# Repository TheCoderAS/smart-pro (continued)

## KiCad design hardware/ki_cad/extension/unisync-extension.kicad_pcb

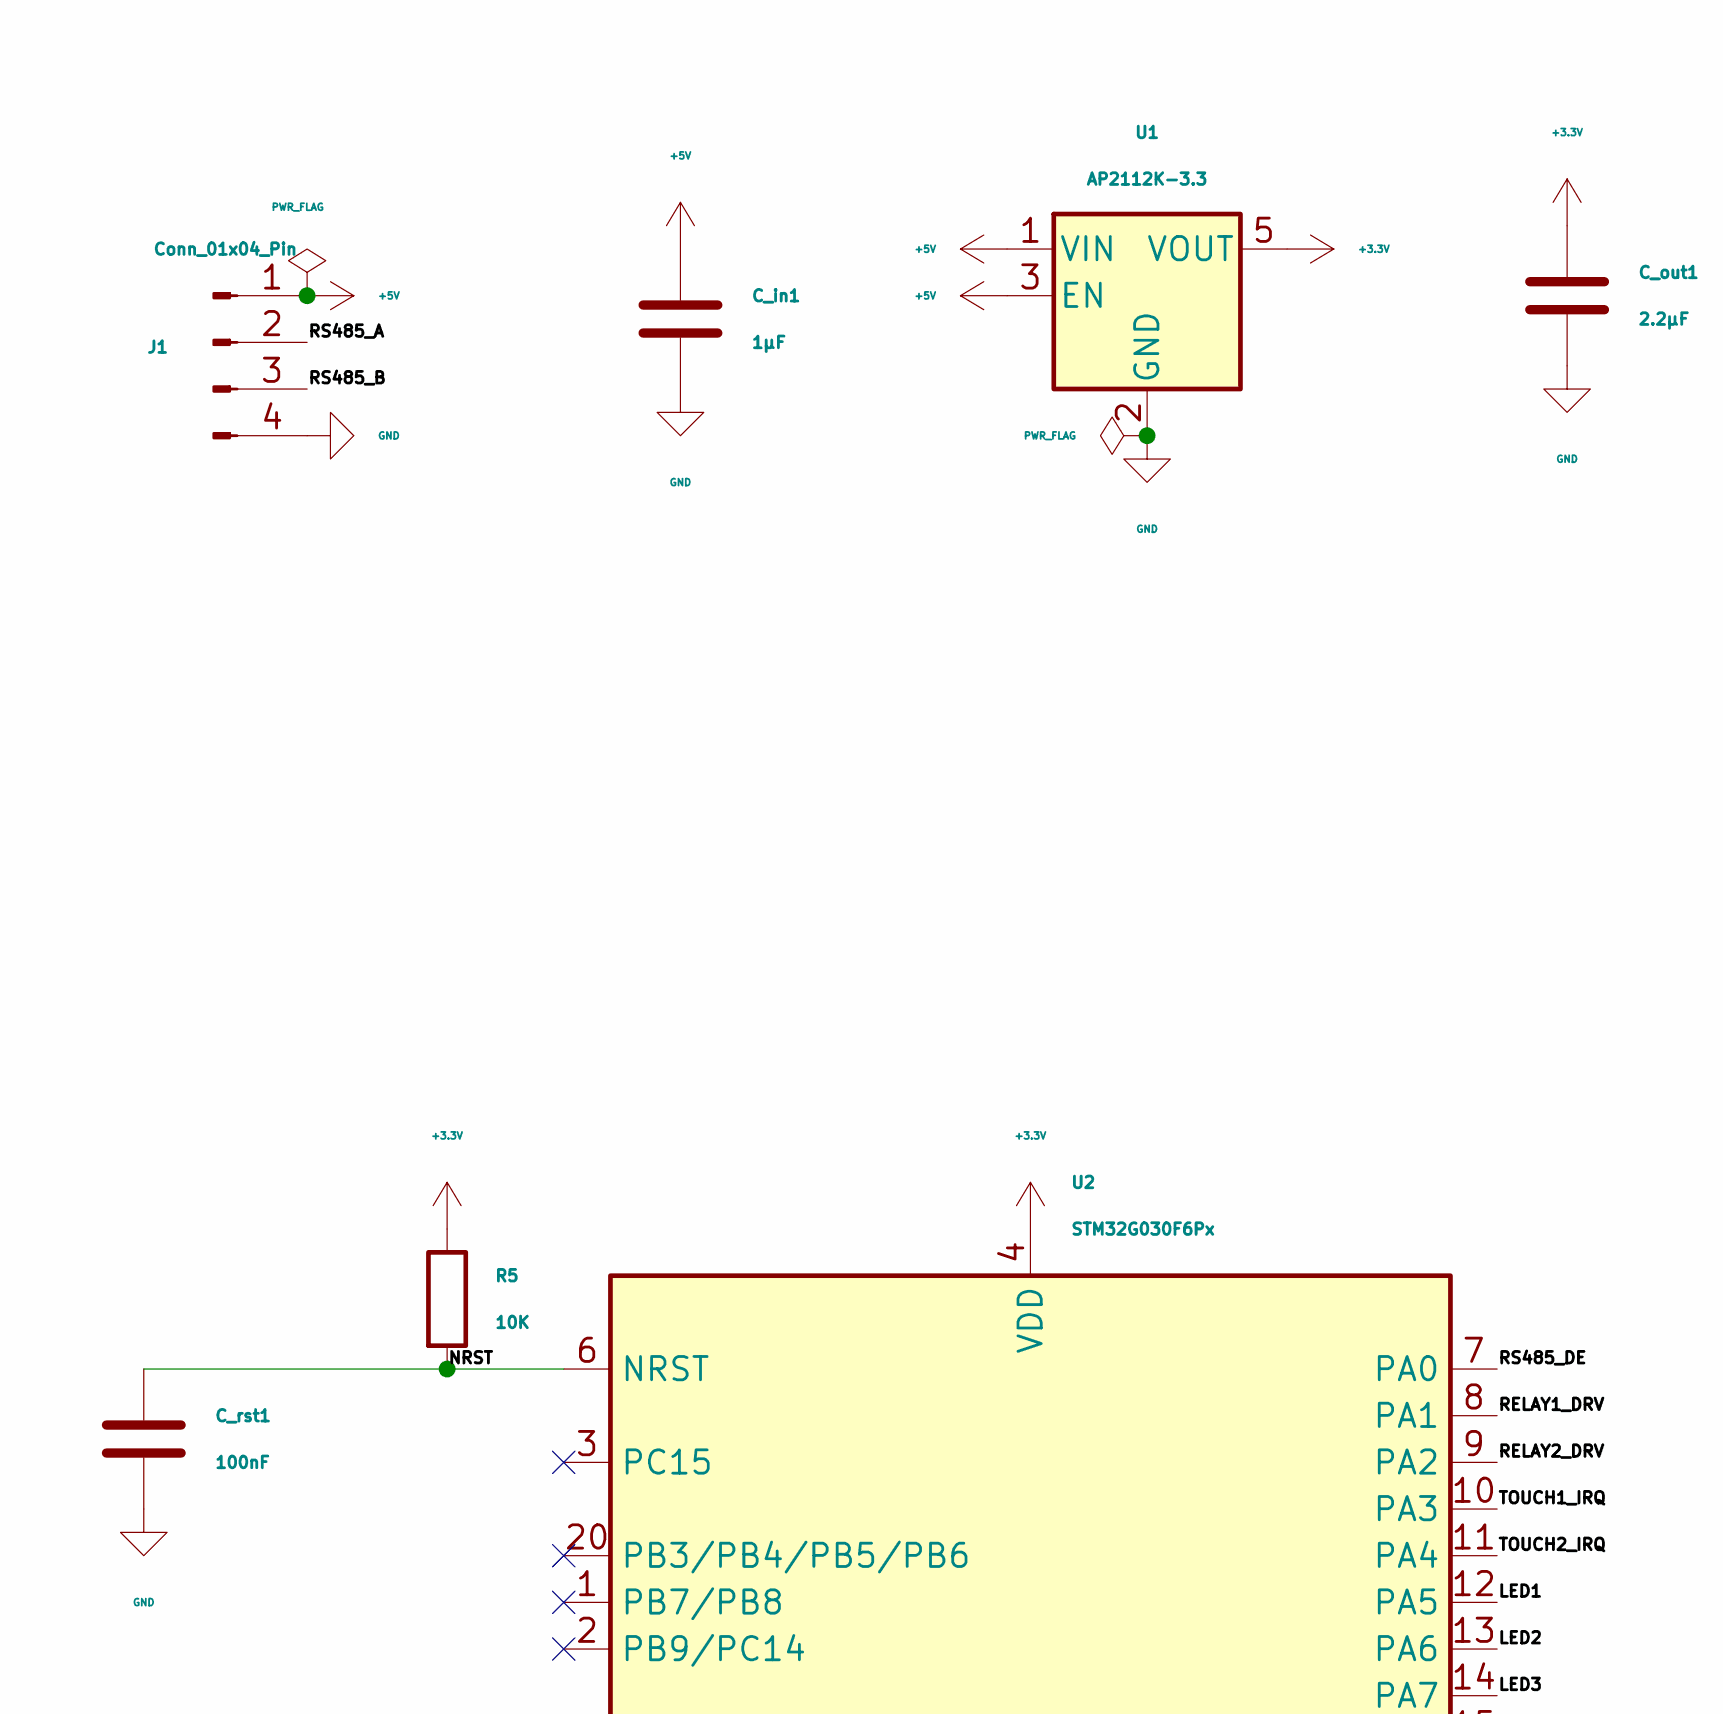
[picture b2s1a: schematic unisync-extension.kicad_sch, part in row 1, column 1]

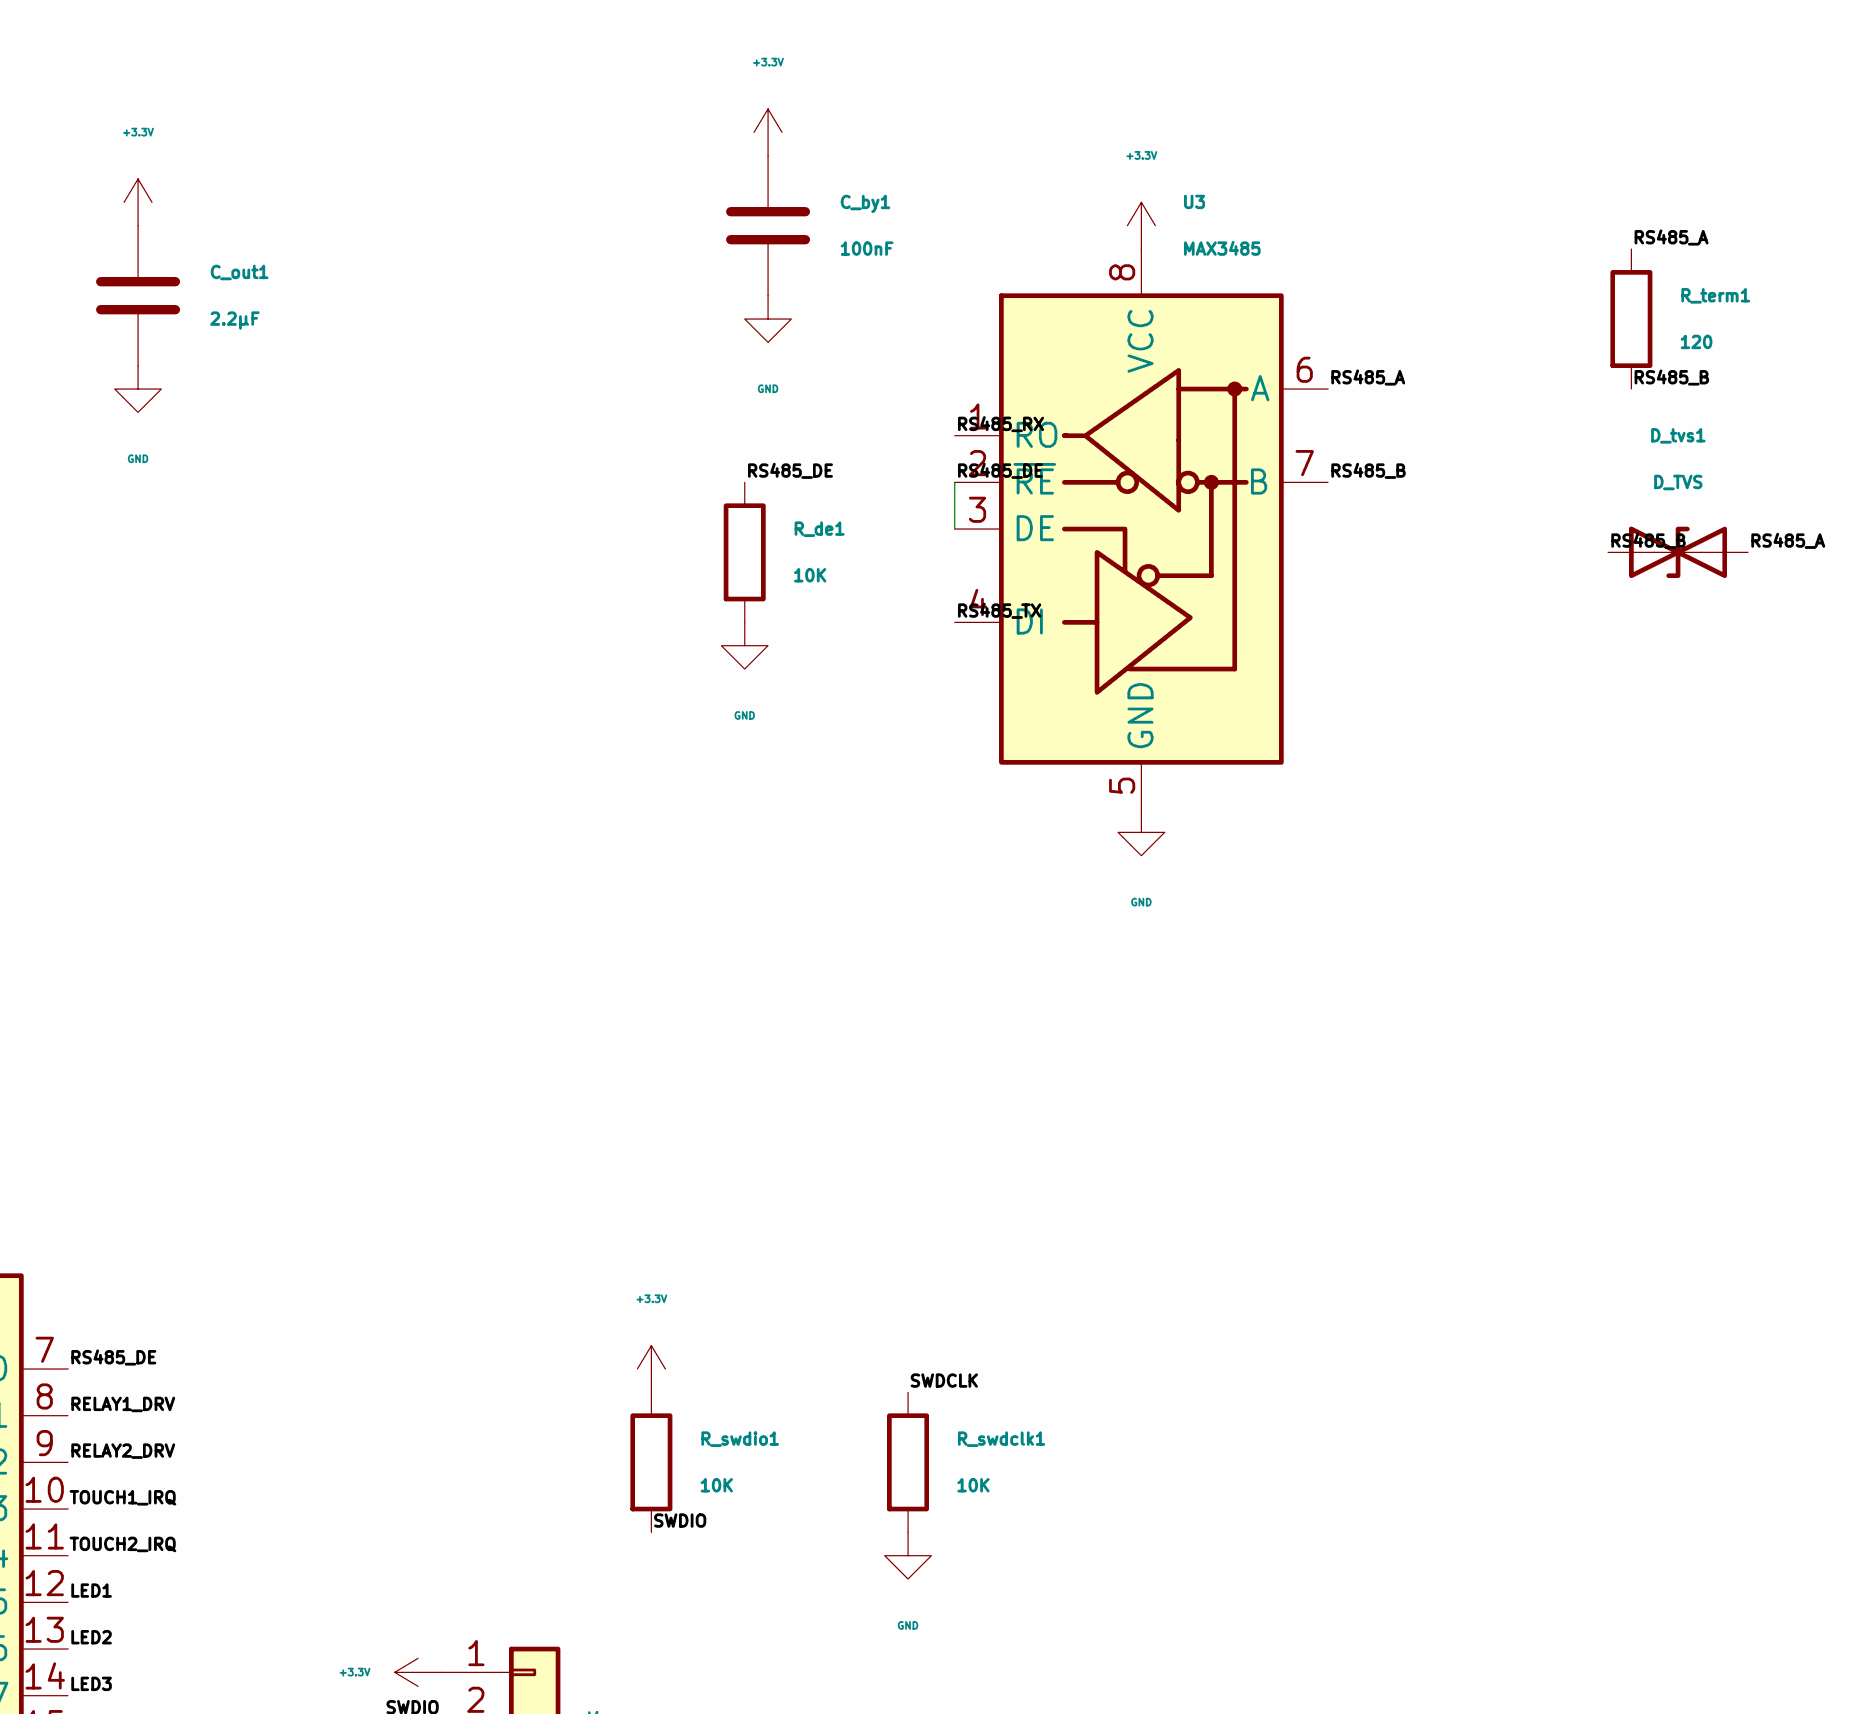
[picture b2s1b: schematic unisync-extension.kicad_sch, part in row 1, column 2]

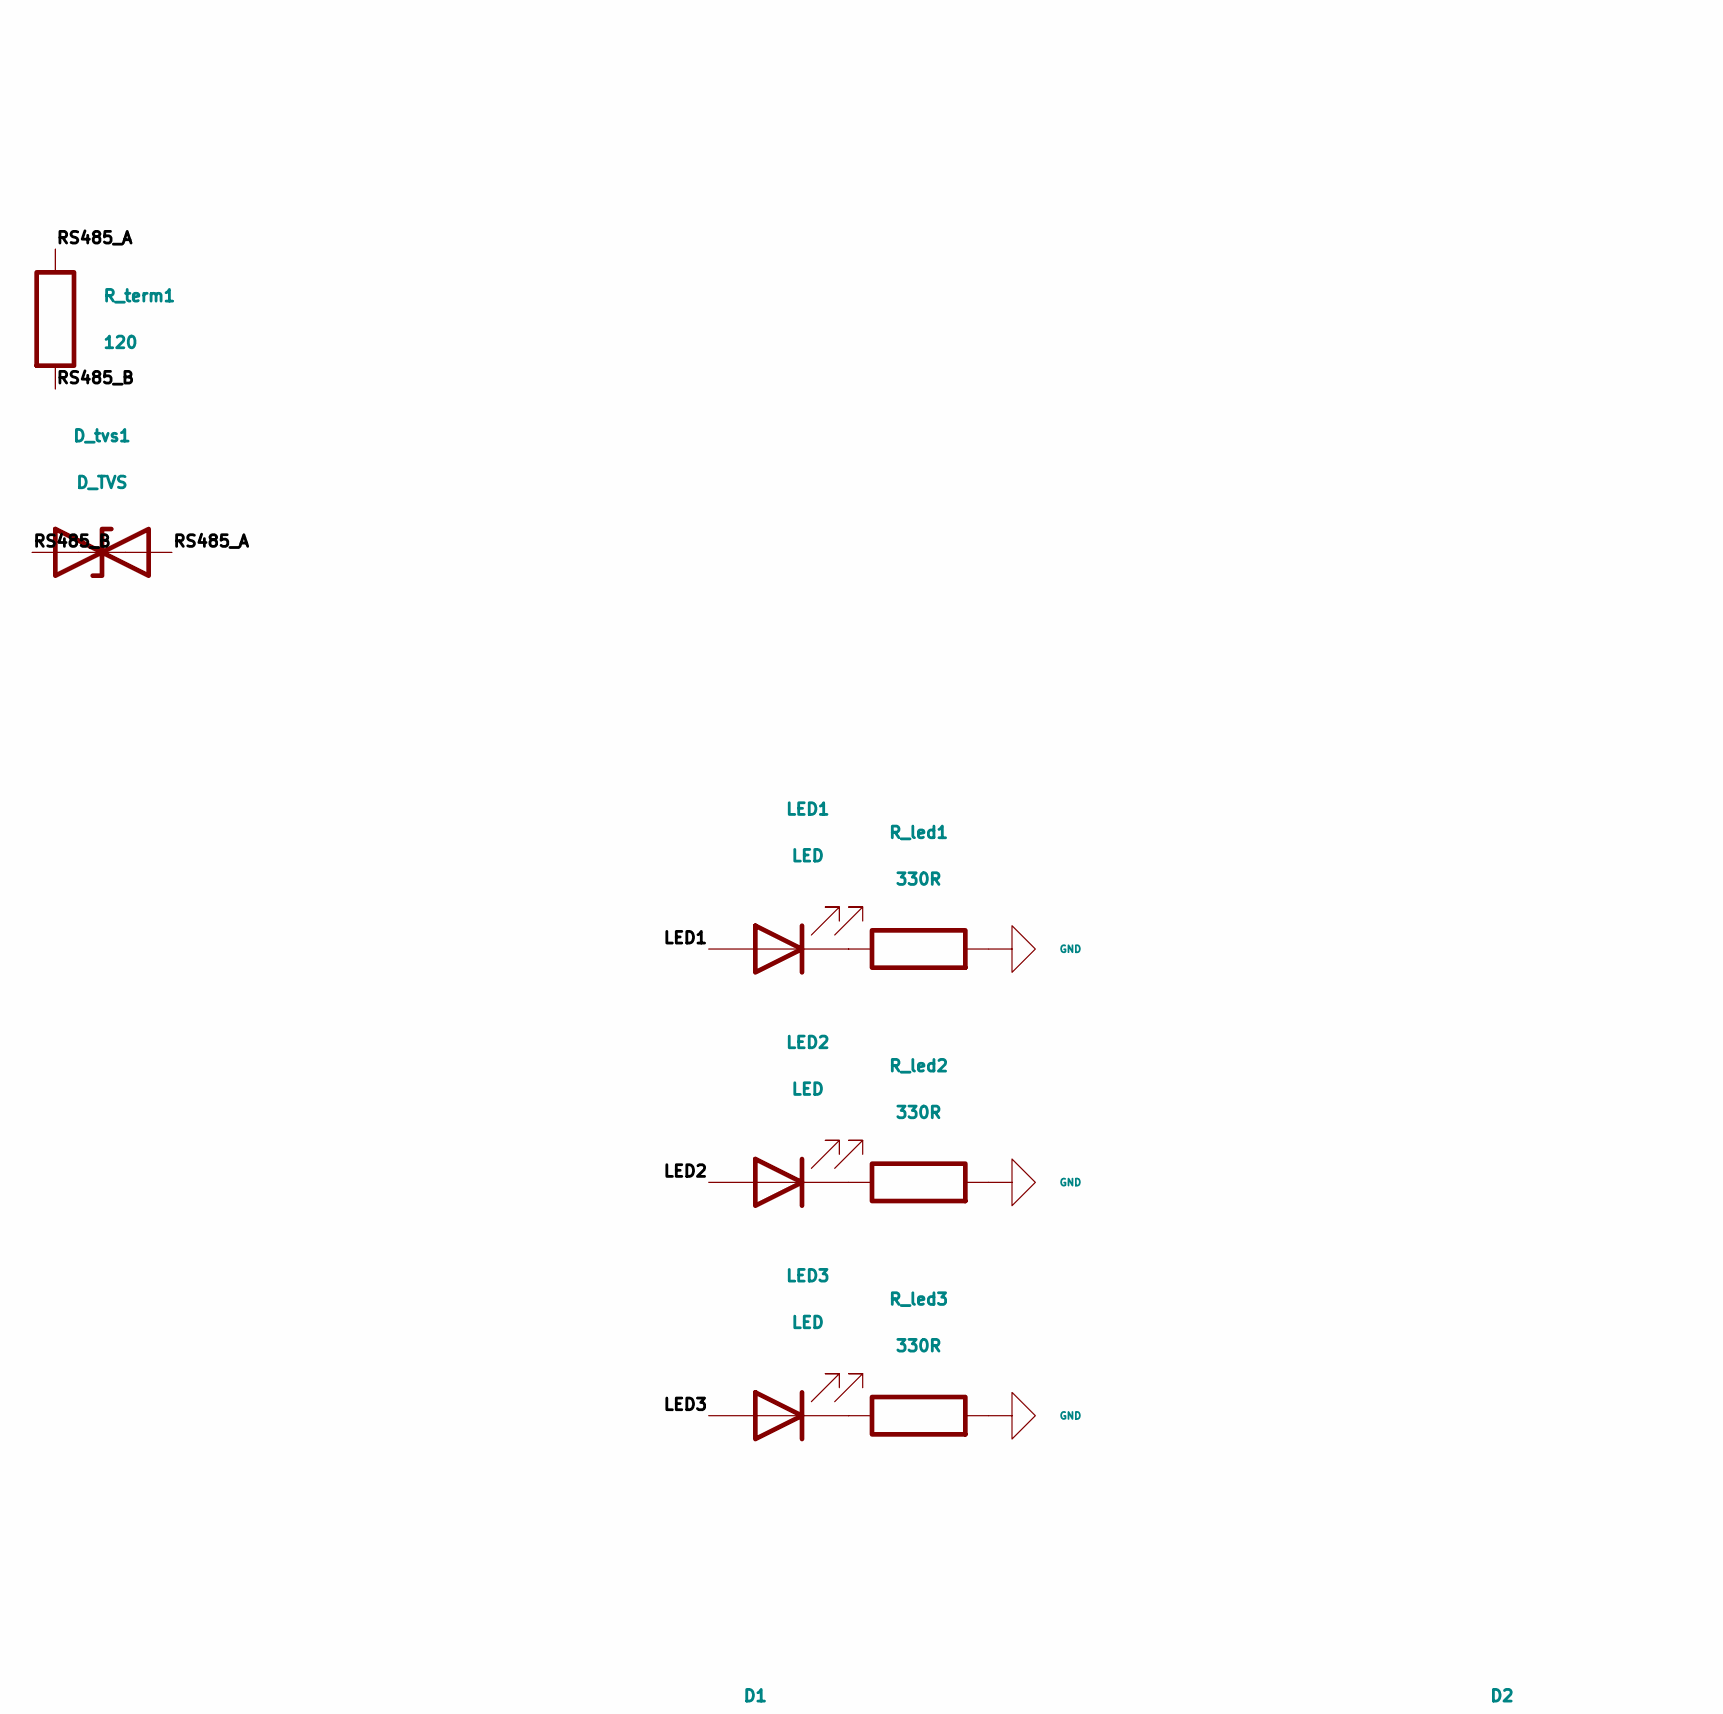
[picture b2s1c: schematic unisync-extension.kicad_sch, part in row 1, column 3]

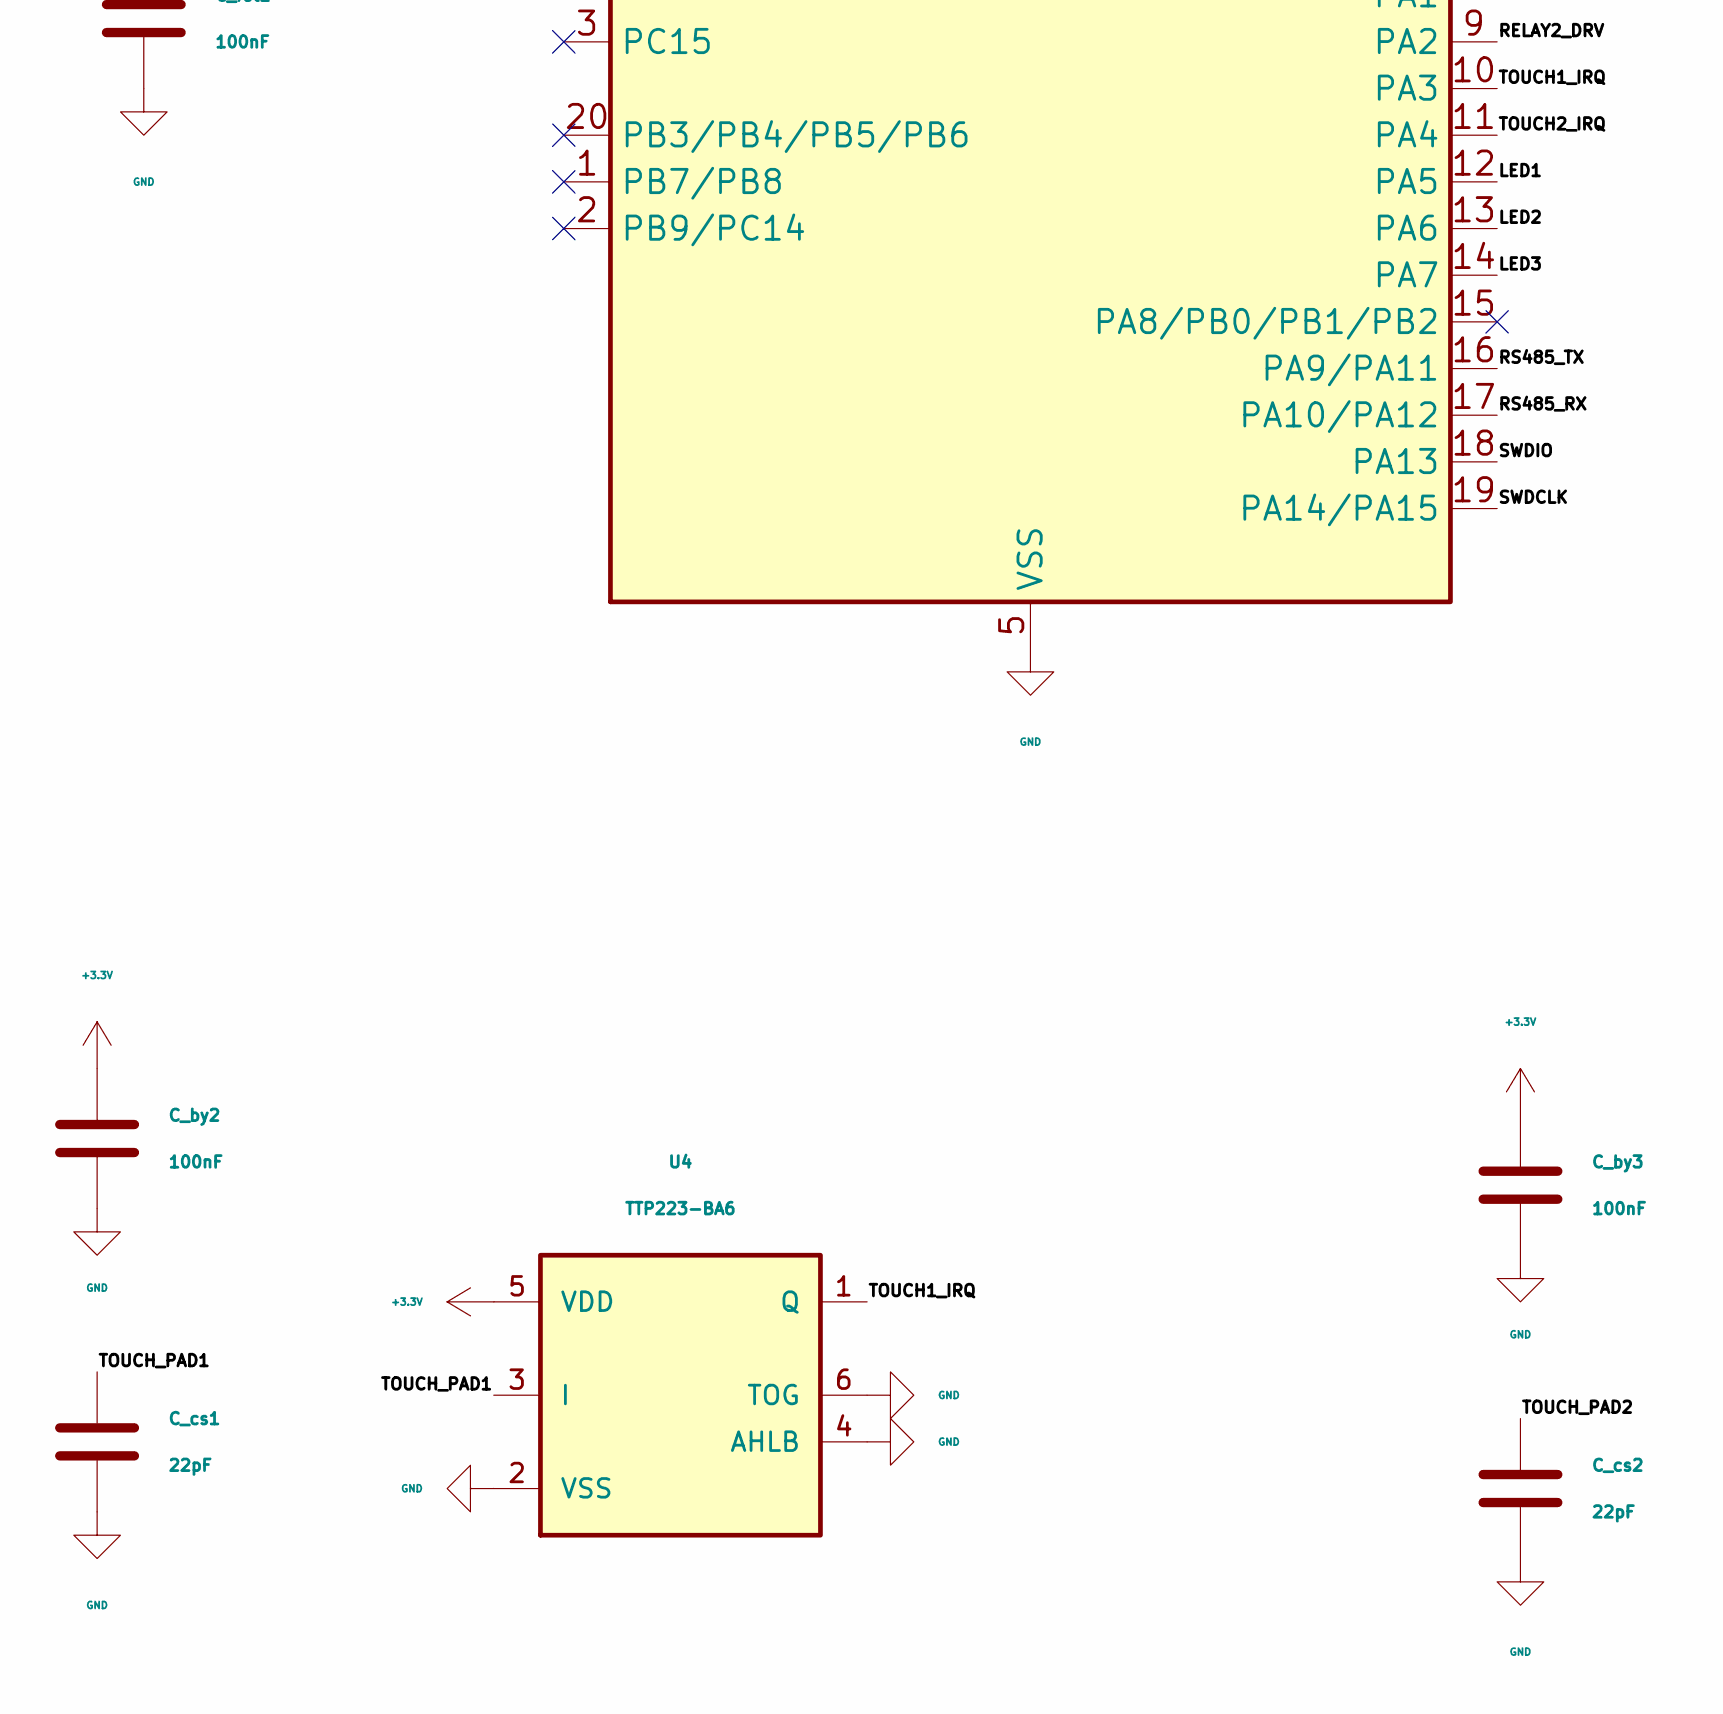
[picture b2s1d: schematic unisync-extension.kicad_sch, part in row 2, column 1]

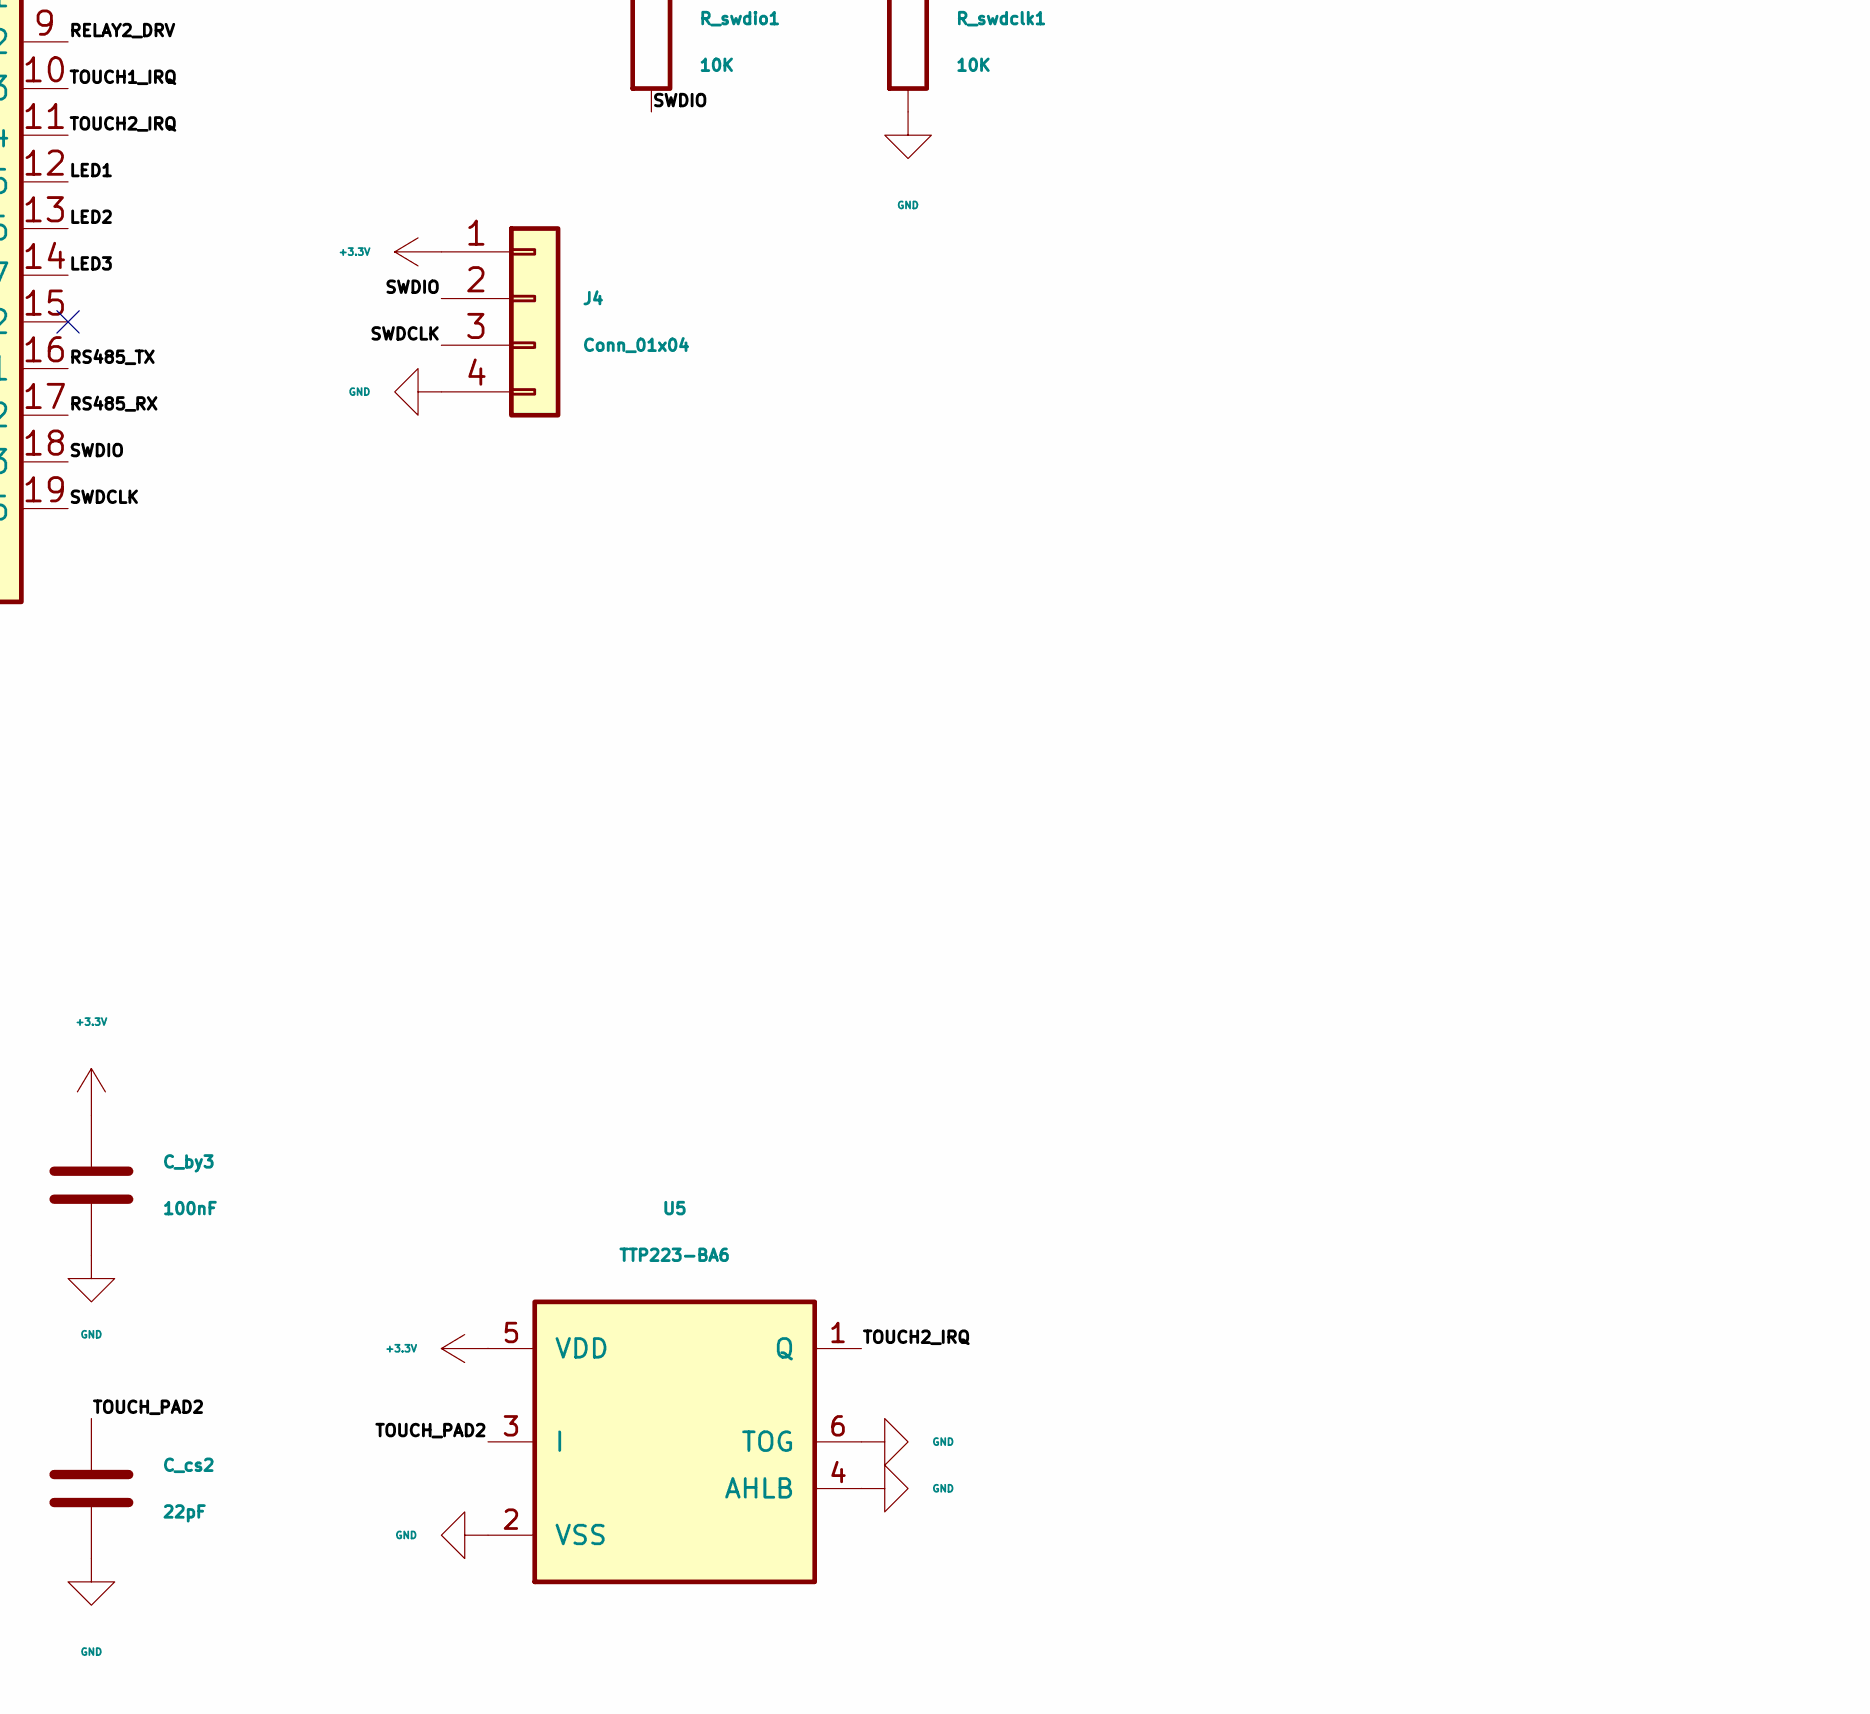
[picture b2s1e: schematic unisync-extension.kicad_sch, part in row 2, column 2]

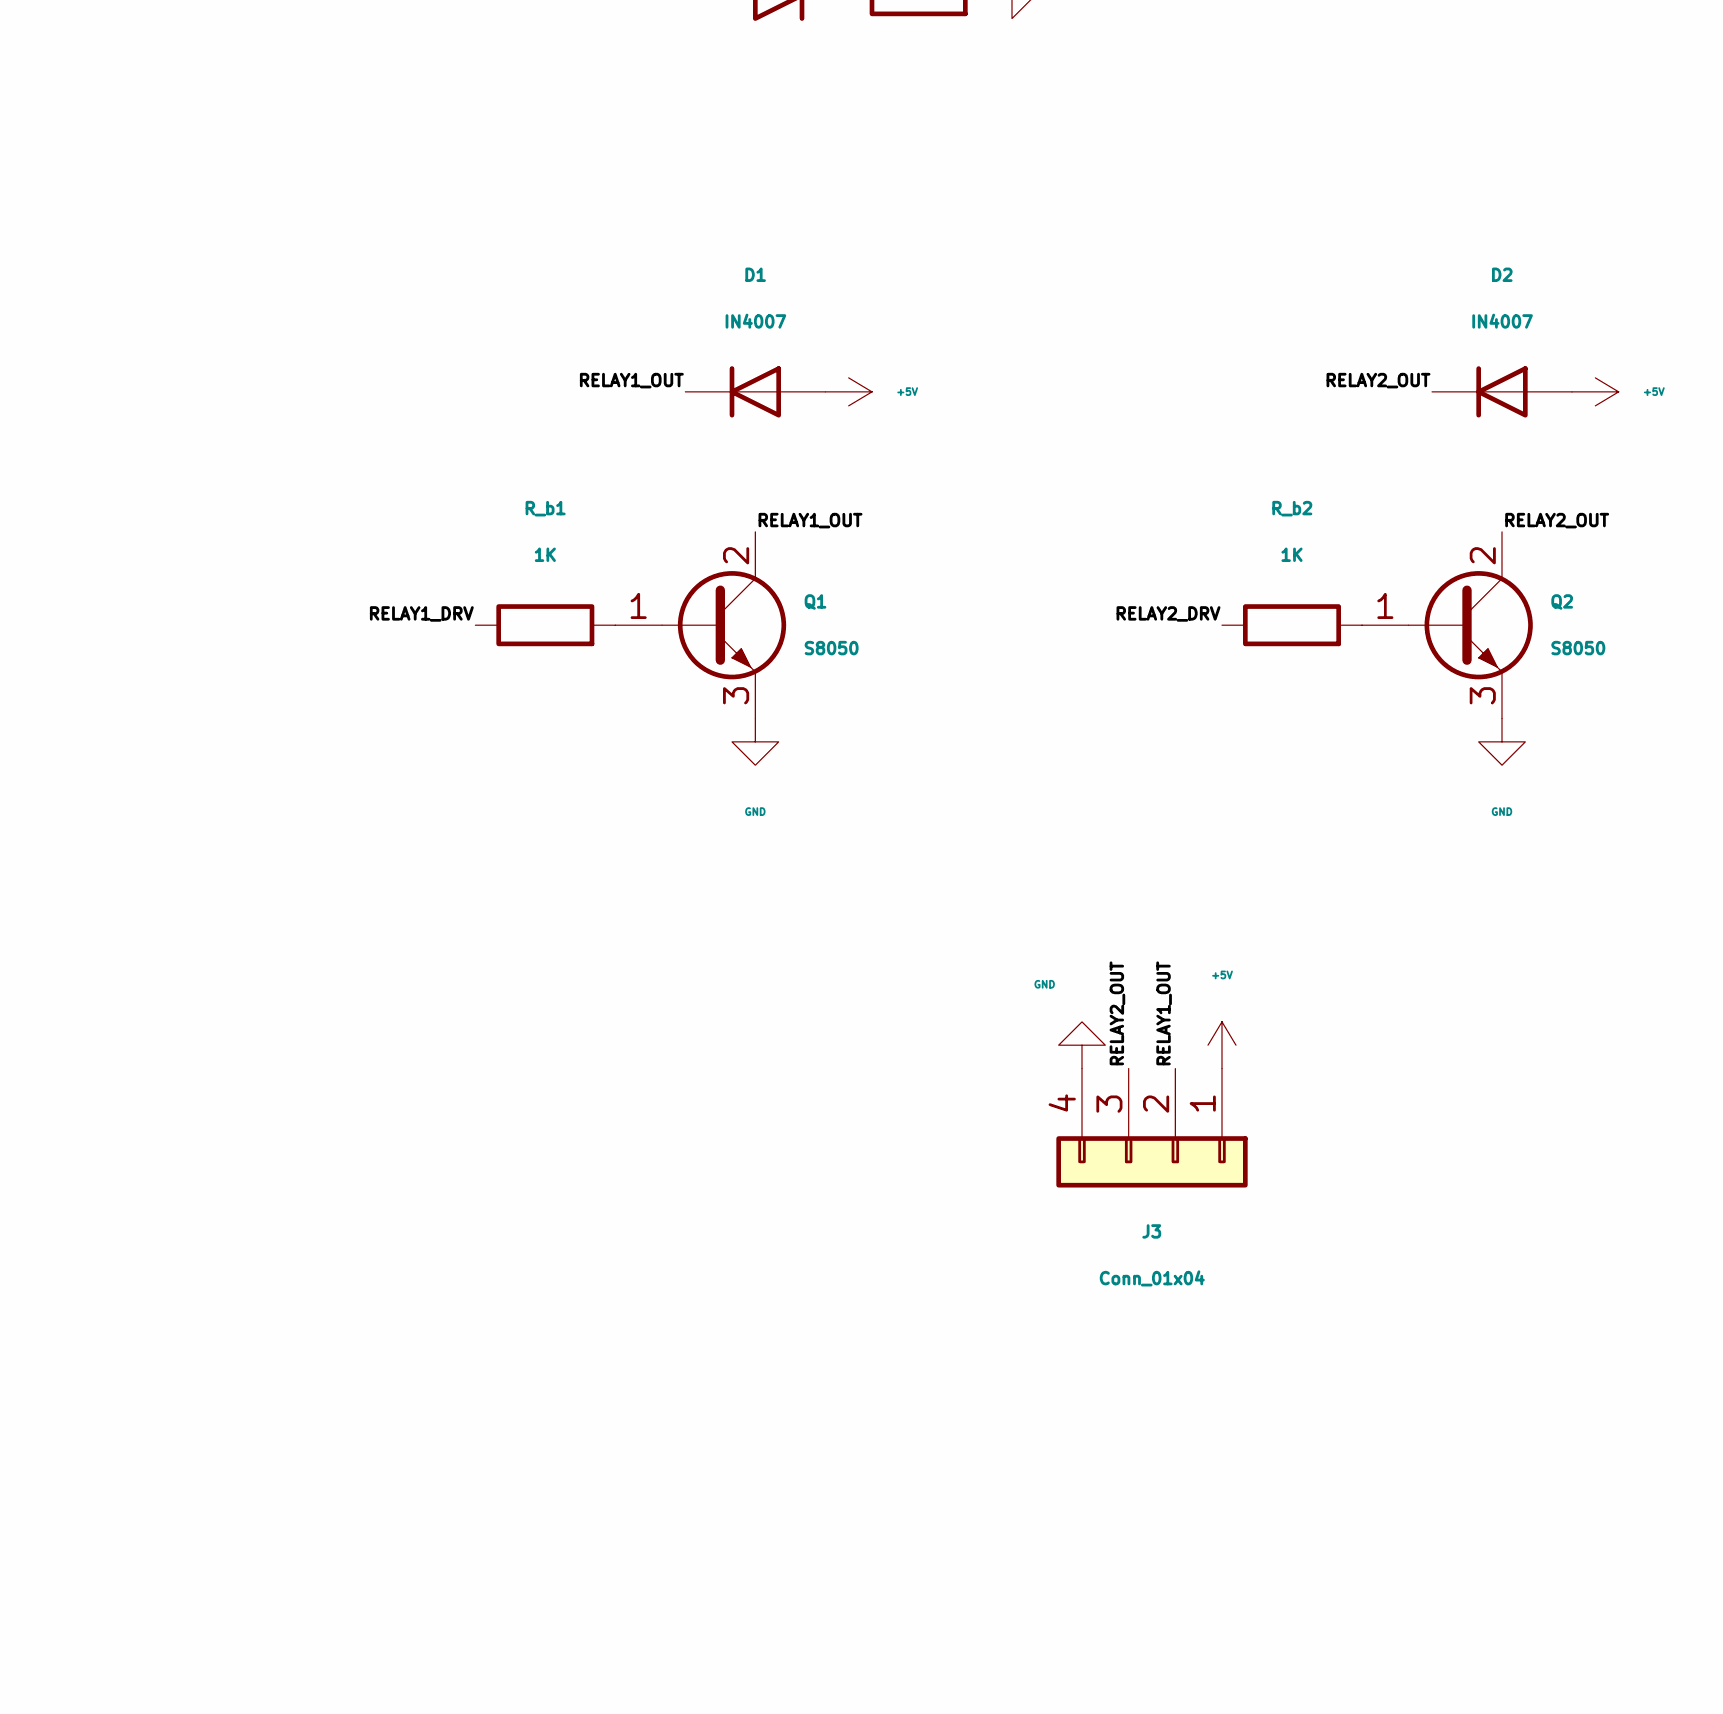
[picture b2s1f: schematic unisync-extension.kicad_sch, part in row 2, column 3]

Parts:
C_by1, C_by2, C_by3: 100nF; C_0402_1005Metric
C_cs1, C_cs2: 22pF; C_0402_1005Metric
C_in1: 1µF; C_0402_1005Metric
C_out1: 2.2µF; C_0402_1005Metric
C_rst1: 100nF; C_0402_1005Metric
D1, D2: IN4007; D_SOD-123
D_tvs1: D_TVS; D_SMB
J1: Conn_01x04_Pin; JST_XH_B4B-XH-A_1x04_P2.50mm_Vertical
J3, J4: Conn_01x04; PinHeader_1x04_P2.54mm_Vertical
LED1, LED2, LED3: LED; LED_0805_2012Metric
Q1, Q2: S8050; SOT-23
R5: 10K; R_0402_1005Metric
R_b1, R_b2: 1K; R_0402_1005Metric
R_de1: 10K; R_0402_1005Metric
R_led1, R_led2, R_led3: 330R; R_0402_1005Metric
R_swdclk1: 10K; R_0402_1005Metric
R_swdio1: 10K; R_0402_1005Metric
R_term1: 120; R_0402_1005Metric
U1: AP2112K-3.3; SOT-23-5
U2: STM32G030F6Px; TSSOP-20_4.4x6.5mm_P0.65mm
U3: MAX3485; SOIC-8_3.9x4.9mm_P1.27mm
U4, U5: TTP223-BA6; SOT-23-6

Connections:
+3.3V: C_by1.1, C_by2.1, C_by3.1, C_out1.1, J4.1, R5.1, R_swdio1.1, U1.5 (VOUT), U2.4 (VDD), U3.8 (VCC), U4.5 (VDD), U5.5 (VDD)
+5V: C_in1.1, D1.2 (A), D2.2 (A), J1.1, J3.1, U1.1 (VIN), U1.3 (EN)
/LED1: LED1.2 (A), U2.12 (PA5)
/LED2: LED2.2 (A), U2.13 (PA6)
/LED3: LED3.2 (A), U2.14 (PA7)
/NRST: C_rst1.1, R5.2, U2.6 (NRST)
/RELAY1_DRV: R_b1.1, U2.8 (PA1)
/RELAY1_OUT: D1.1 (K), J3.2, Q1.2 (C)
/RELAY2_DRV: R_b2.1, U2.9 (PA2)
/RELAY2_OUT: D2.1 (K), J3.3, Q2.2 (C)
/RS485_A: D_tvs1.2 (A2), J1.2, R_term1.1, U3.6 (A)
/RS485_B: D_tvs1.1 (A1), J1.3, R_term1.2, U3.7 (B)
/RS485_DE: R_de1.1, U2.7 (PA0), U3.2 (~RE), U3.3 (DE)
/RS485_RX: U2.17 (PA10/PA12), U3.1 (RO)
/RS485_TX: U2.16 (PA9/PA11), U3.4 (DI)
/SWDCLK: J4.3, R_swdclk1.1, U2.19 (PA14/PA15)
/SWDIO: J4.2, R_swdio1.2, U2.18 (PA13)
/TOUCH1_IRQ: U2.10 (PA3), U4.1 (Q)
/TOUCH2_IRQ: U2.11 (PA4), U5.1 (Q)
/TOUCH_PAD1: C_cs1.1, U4.3 (I)
/TOUCH_PAD2: C_cs2.1, U5.3 (I)
GND: C_by1.2, C_by2.2, C_by3.2, C_cs1.2, C_cs2.2, C_in1.2, C_out1.2, C_rst1.2, J1.4, J3.4, J4.4, Q1.3 (E), Q2.3 (E), R_de1.2, R_led1.2, R_led2.2, R_led3.2, R_swdclk1.2, U1.2 (GND), U2.5 (VSS), U3.5 (GND), U4.2 (VSS), U4.4 (AHLB), U4.6 (TOG), U5.2 (VSS), U5.4 (AHLB), U5.6 (TOG)
unnamed: LED1.1 (K), R_led1.1
unnamed: LED2.1 (K), R_led2.1
unnamed: LED3.1 (K), R_led3.1
unnamed: Q1.1 (B), R_b1.2
unnamed: Q2.1 (B), R_b2.2

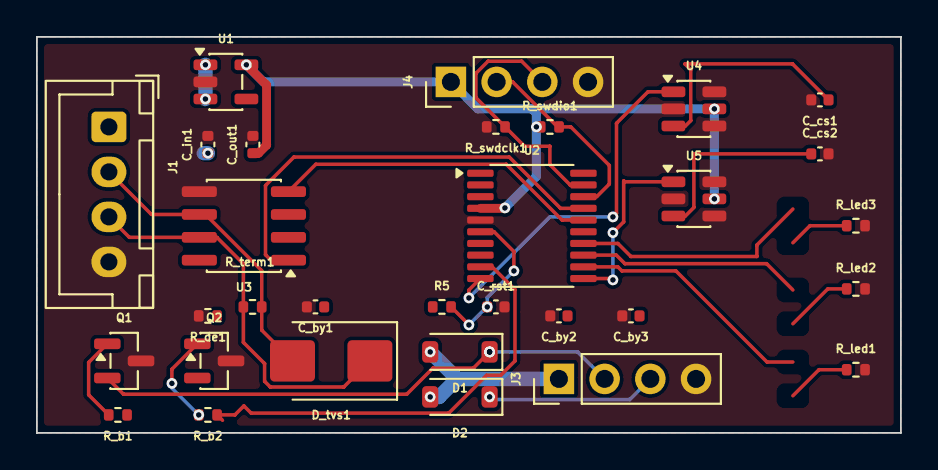
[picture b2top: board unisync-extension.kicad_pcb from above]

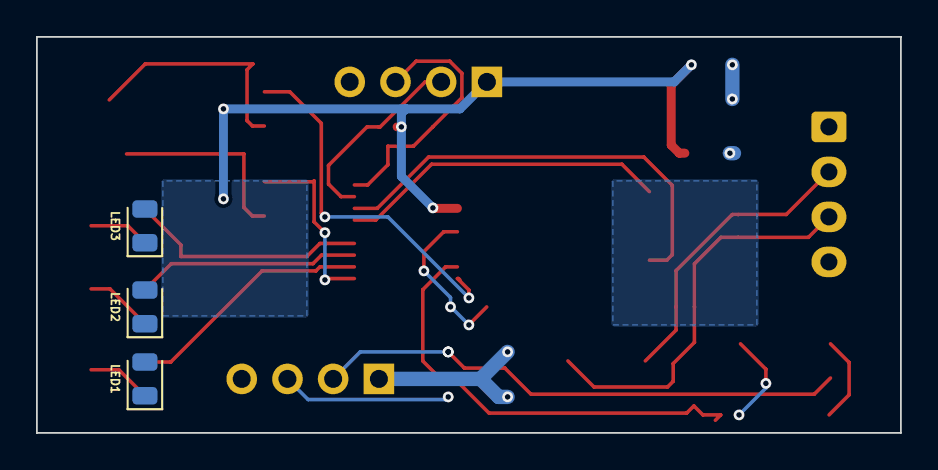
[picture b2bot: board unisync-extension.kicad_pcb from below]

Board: 2 copper layers, 48.0 x 22.0 mm, 34 parts (3 on the bottom side), 27 nets.

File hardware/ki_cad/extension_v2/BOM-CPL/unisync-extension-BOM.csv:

"Id";"Designator";"Footprint";"Quantity";"Designation";"Supplier and ref";
1;"C_by1, C_by2, C_by3, C_rst1";"C_0402_1005Metric";4;"100nF";;;
2;"C_cs1, C_cs2";"C_0402_1005Metric";2;"22pF";;;
3;"C_in1";"C_0402_1005Metric";1;"1µF";;;
4;"C_out1";"C_0402_1005Metric";1;"2.2µF";;;
5;"D1, D2";"D_SOD-123";2;"IN4007";;;
6;"D_tvs1";"D_SMB";1;"D_TVS";;;
7;"J1";"PinHeader_1x04_P2.54mm_Vertical";1;"Conn_01x04_Pin";;;
8;"J3, J4";"PinHeader_1x04_P2.54mm_Vertical";2;"Conn_01x04";;;
9;"LED1, LED2, LED3";"LED_0805_2012Metric";3;"LED";;;
10;"Q1, Q2";"SOT-23";2;"S8050";;;
11;"R5, R_de1, R_swdclk1, R_swdio1";"R_0402_1005Metric";4;"10K";;;
12;"R_b1, R_b2";"R_0402_1005Metric";2;"1K";;;
13;"R_led1, R_led2, R_led3";"R_0402_1005Metric";3;"330R";;;
14;"R_term1";"R_0402_1005Metric";1;"120";;;
15;"SW1";"SW_SPST_B3U-1000P";1;"SW_Push";;;
16;"U1";"SOT-23-5";1;"AP2112K-3.3";;;
17;"U2";"TSSOP-20_4.4x6.5mm_P0.65mm";1;"STM32G030F6Px";;;
18;"U3";"SOIC-8_3.9x4.9mm_P1.27mm";1;"MAX3485";;;
19;"U4, U5";"SOT-23-6";2;"TTP223-BA6";;;
